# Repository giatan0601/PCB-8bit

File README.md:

# PCB-8bit

Dự án thiết kế mạch in (PCB) cho bộ cộng 8-bit, được xây dựng từ các khối **full adder 1-bit** ghép nối tiếp, kèm theo mạch **giao tiếp (interface)** để nhập dữ liệu và hiển thị kết quả.

## Mục lục

- [Giới thiệu](#giới-thiệu)
- [Cấu trúc thư mục](#cấu-trúc-thư-mục)
- [Nguyên lý hoạt động](#nguyên-lý-hoạt-động)
- [Công cụ sử dụng](#công-cụ-sử-dụng)

- [Hướng dẫn sử dụng](#hướng-dẫn-sử-dụng)
- [Hình ảnh](#hình-ảnh)
- [Tác giả](#tác-giả)

## Giới thiệu

Mục tiêu của dự án là thiết kế và chế tạo một bộ cộng 8-bit trên PCB, theo hướng đi từ khối nhỏ đến hệ thống hoàn chỉnh:

1. Thiết kế và kiểm tra khối full adder 1-bit.
2. Ghép 8 khối full adder thành bộ cộng 8-bit (kiểu ripple-carry).
3. Thiết kế mạch interface để nhập hai toán hạng và quan sát kết quả.

## Cấu trúc thư mục

```
PCB-8bit/
├── fulladder1bit/
│   └── 1bit/          # Thiết kế schematic + PCB của khối full adder 1-bit
└── interface/         # Thiết kế mạch giao tiếp (nhập liệu / hiển thị)
```

| Thư mục | Mô tả |
| --- | --- |
| `fulladder1bit/1bit` | Khối full adder 1-bit, là đơn vị cơ bản để xây dựng bộ cộng 8-bit |
| `interface` | Mạch giao tiếp giữa người dùng và bộ cộng |

## Nguyên lý hoạt động

Mỗi khối full adder 1-bit nhận vào 3 tín hiệu: `A`, `B` và `Cin` (số nhớ từ bit trước), cho ra `Sum` và `Cout` (số nhớ sang bit sau).

**Công thức logic:**

```
Sum  = A ⊕ B ⊕ Cin
Cout = (A · B) + (Cin · (A ⊕ B))
```

**Bảng chân trị:**

| A | B | Cin | Sum | Cout |
|:-:|:-:|:---:|:---:|:----:|
| 0 | 0 | 0 | 0 | 0 |
| 0 | 0 | 1 | 1 | 0 |
| 0 | 1 | 0 | 1 | 0 |
| 0 | 1 | 1 | 0 | 1 |
| 1 | 0 | 0 | 1 | 0 |
| 1 | 0 | 1 | 0 | 1 |
| 1 | 1 | 0 | 0 | 1 |
| 1 | 1 | 1 | 1 | 1 |

**Bộ cộng 8-bit (ripple-carry):** `Cout` của khối thứ *i* được nối vào `Cin` của khối thứ *i+1*. `Cin` của khối đầu tiên nối mức 0.

```
A7 B7      A1 B1      A0 B0
 │  │       │  │       │  │
┌▼──▼┐     ┌▼──▼┐     ┌▼──▼┐
│ FA │ ... │ FA │◄────│ FA │◄── Cin = 0
└┬──┬┘     └┬──┬┘     └┬──┬┘
 │  │       │  │       │  │
Cout S7     C1 S1      C0 S0
```

## Công cụ sử dụng

- Phần mềm thiết kế PCB: `KiCad `

## Hướng dẫn sử dụng

**1. Tải mã nguồn**

```bash
git clone https://github.com/giatan0601/PCB-8bit.git
cd PCB-8bit
```

**2. Mở thiết kế**

- Khối full adder 1-bit: mở project trong thư mục `fulladder1bit/1bit`.
- Mạch giao tiếp: mở project trong thư mục `interface`.

**3. Xuất file sản xuất (Gerber)**

Xuất file Gerber và file khoan từ phần mềm thiết kế, sau đó gửi cho nhà sản xuất PCB.

**4. Kiểm tra mạch**

Cấp nguồn `5V`, đặt các giá trị `A`, `B`, `Cin` và đối chiếu `Sum`, `Cout` với bảng chân trị ở trên.

## Hình ảnh

## Tác giả

- **giatan0601** – [GitHub](https://github.com/giatan0601)

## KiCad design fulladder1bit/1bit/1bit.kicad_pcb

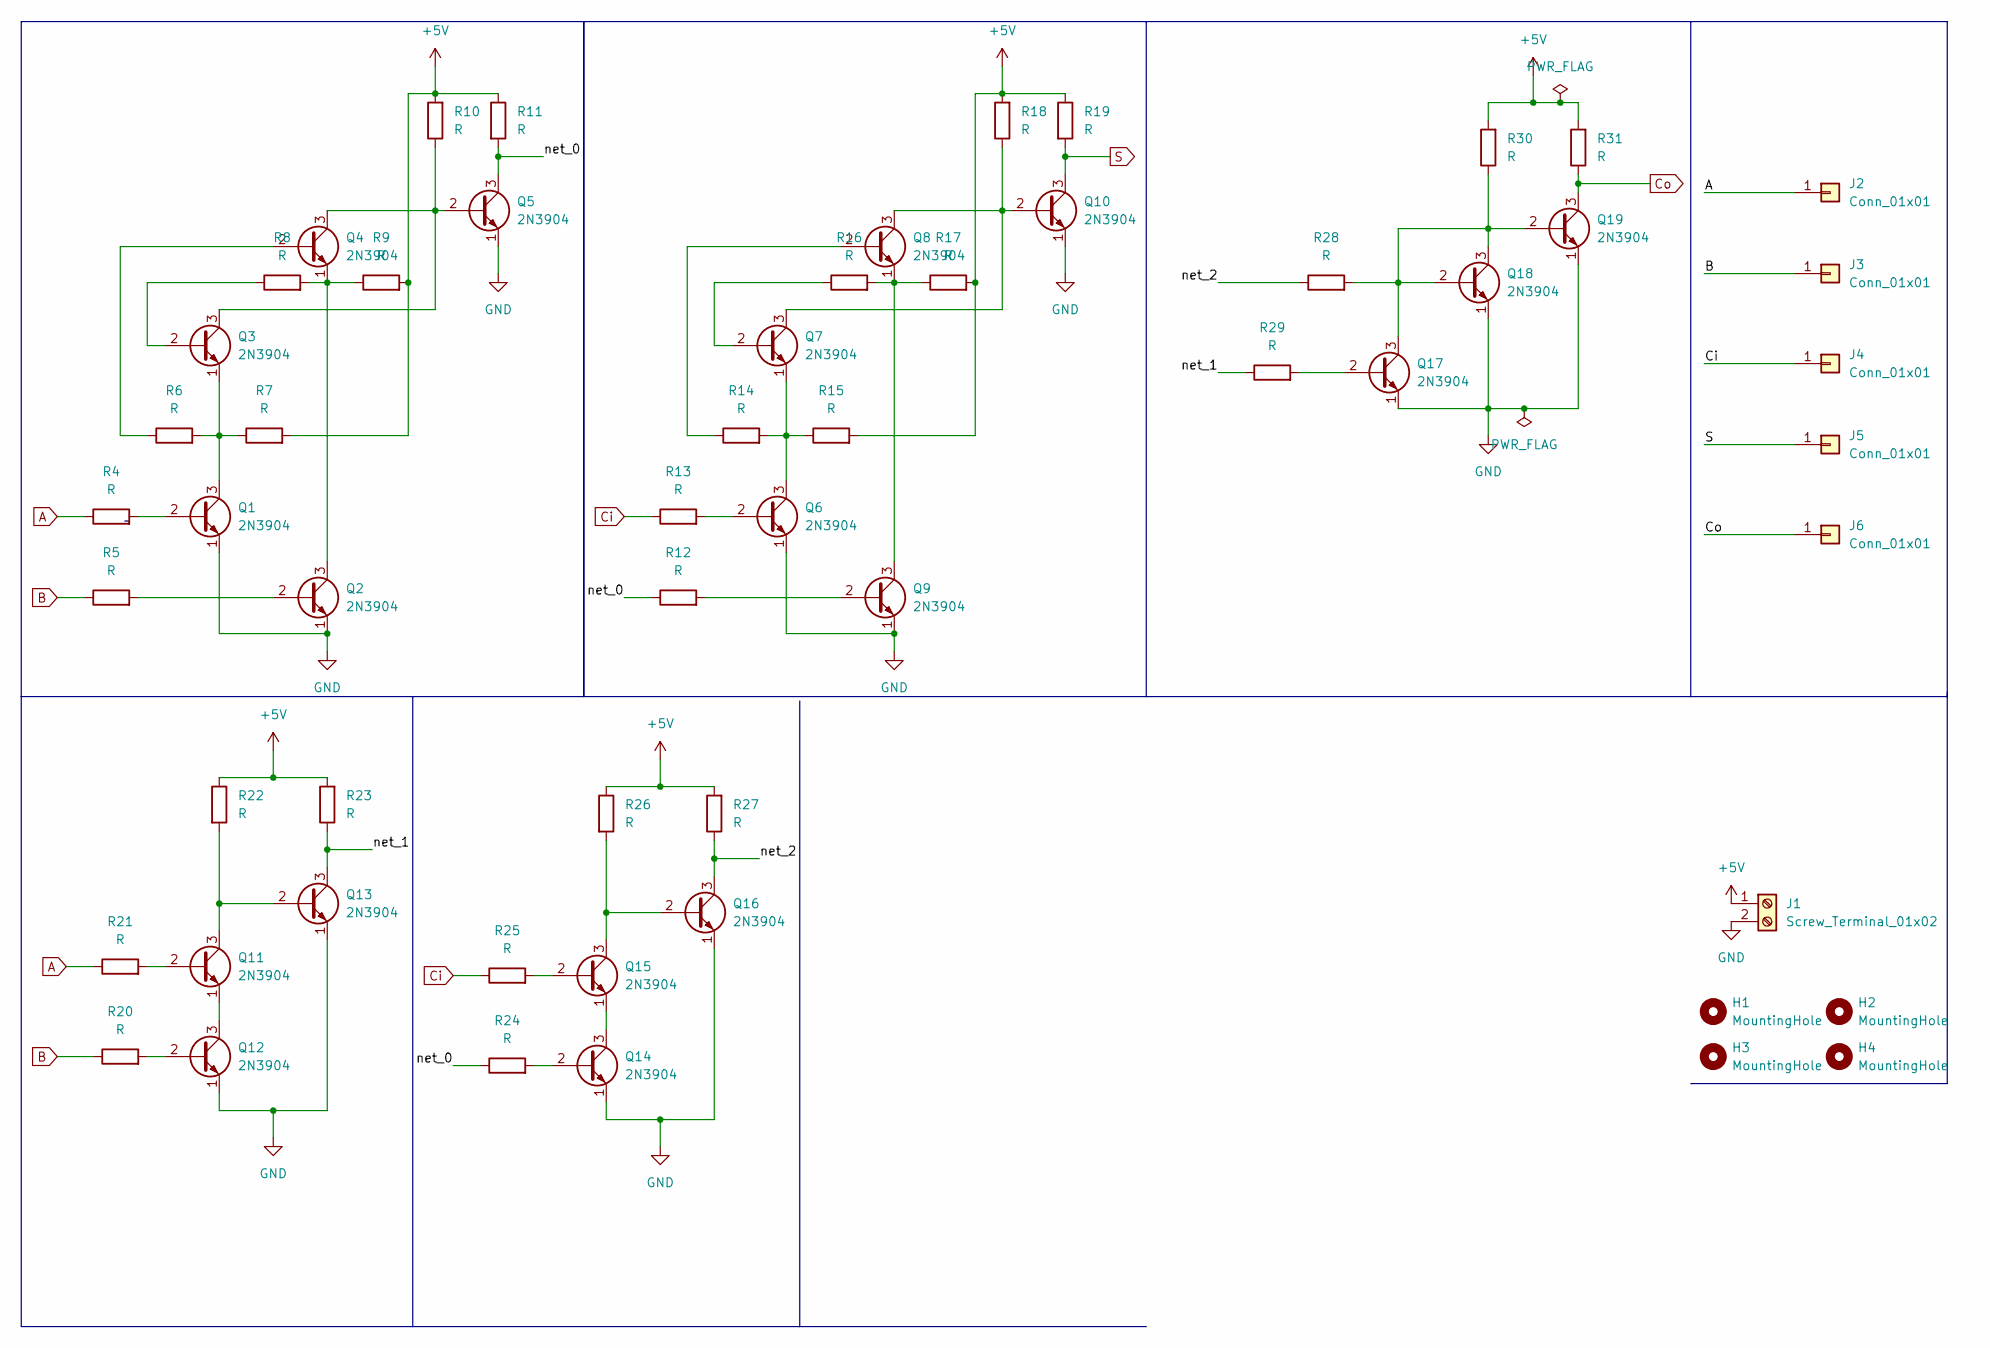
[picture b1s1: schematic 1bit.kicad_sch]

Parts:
H1, H2, H3, H4: MountingHole; MountingHole_2.7mm
J1: Screw_Terminal_01x02; TerminalBlock_Phoenix_MKDS-1,5-2_1x02_P5.00mm_Horizontal
J2, J3, J4, J5, J6: Conn_01x01; PinHeader_1x01_P2.54mm_Horizontal
Q1, Q2, Q3, Q4, Q5, Q6, Q7, Q8, Q9, Q10, Q11, Q12, Q13, Q14, Q15, Q16, Q17, Q18, Q19: 2N3904; TO-92_Inline_Wide
R4, R5, R6, R7, R8, R9, R10, R11, R12, R13, R14, R15, R16, R17, R18, R19, R20, R21, R22, R23, R24, R25, R26, R27, R28, R29, R30, R31: R; R_Axial_DIN0207_L6.3mm_D2.5mm_P7.62mm_Horizontal

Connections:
+5V: J1.1, R7.2, R9.2, R10.2, R11.1, R15.2, R17.2, R18.2, R19.1, R22.1, R23.2, R26.1, R27.2, R30.2, R31.2
/net_0: Q5.3 (C), R11.2, R12.1, R24.1
/net_1: Q13.3 (C), R23.1, R29.1
/net_2: Q16.3 (C), R27.1, R28.1
A: J2.1 (Pin_1_1), R4.1, R21.1
B: J3.1 (Pin_1_1), R5.1, R20.1
Ci: J4.1 (Pin_1_1), R13.1, R25.1
Co: J6.1 (Pin_1_1), Q19.3 (C), R31.1
GND: J1.2, Q1.1 (E), Q2.1 (E), Q5.1 (E), Q6.1 (E), Q9.1 (E), Q10.1 (E), Q12.1 (E), Q13.1 (E), Q14.1 (E), Q16.1 (E), Q17.1 (E), Q18.1 (E), Q19.1 (E)
unnamed: Q1.2 (B), R4.2
unnamed: Q1.3 (C), Q3.1 (E), R6.2, R7.1
unnamed: Q2.2 (B), R5.2
unnamed: Q2.3 (C), Q4.1 (E), R8.2, R9.1
unnamed: Q3.2 (B), R8.1
unnamed: Q3.3 (C), Q4.3 (C), Q5.2 (B), R10.1
unnamed: Q4.2 (B), R6.1
unnamed: Q6.2 (B), R13.2
unnamed: Q6.3 (C), Q7.1 (E), R14.2, R15.1
unnamed: Q7.2 (B), R16.1
unnamed: Q8.2 (B), R14.1
unnamed: Q8.1 (E), Q9.3 (C), R16.2, R17.1
unnamed: Q9.2 (B), R12.2
unnamed: Q7.3 (C), Q8.3 (C), Q10.2 (B), R18.1
unnamed: Q11.2 (B), R21.2
unnamed: Q11.3 (C), Q13.2 (B), R22.2
unnamed: Q11.1 (E), Q12.3 (C)
unnamed: Q12.2 (B), R20.2
unnamed: Q14.2 (B), R24.2
unnamed: Q14.3 (C), Q15.1 (E)
unnamed: Q15.2 (B), R25.2
unnamed: Q15.3 (C), Q16.2 (B), R26.2
unnamed: Q17.2 (B), R29.2
unnamed: Q17.3 (C), Q18.2 (B), Q18.3 (C), Q19.2 (B), R28.2, R30.1
S: J5.1 (Pin_1_1), Q10.3 (C), R19.2

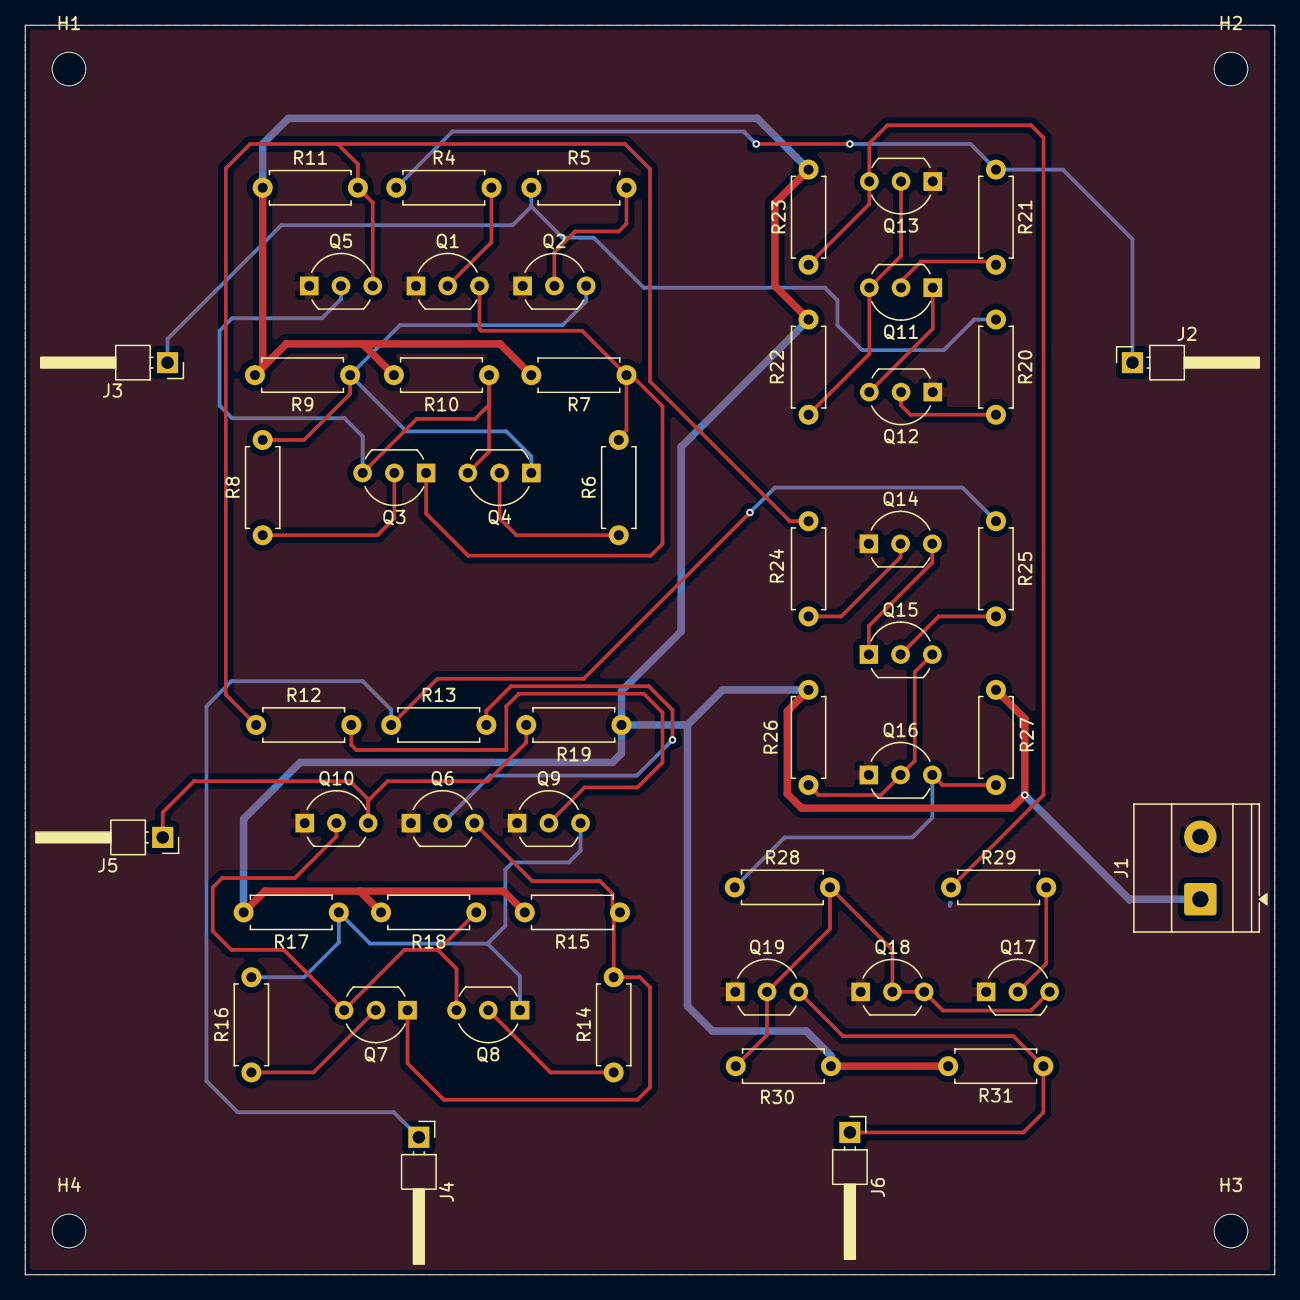
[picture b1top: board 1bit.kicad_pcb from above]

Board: 2 copper layers, 100.0 x 100.0 mm, 57 parts (0 on the bottom side), 34 nets.

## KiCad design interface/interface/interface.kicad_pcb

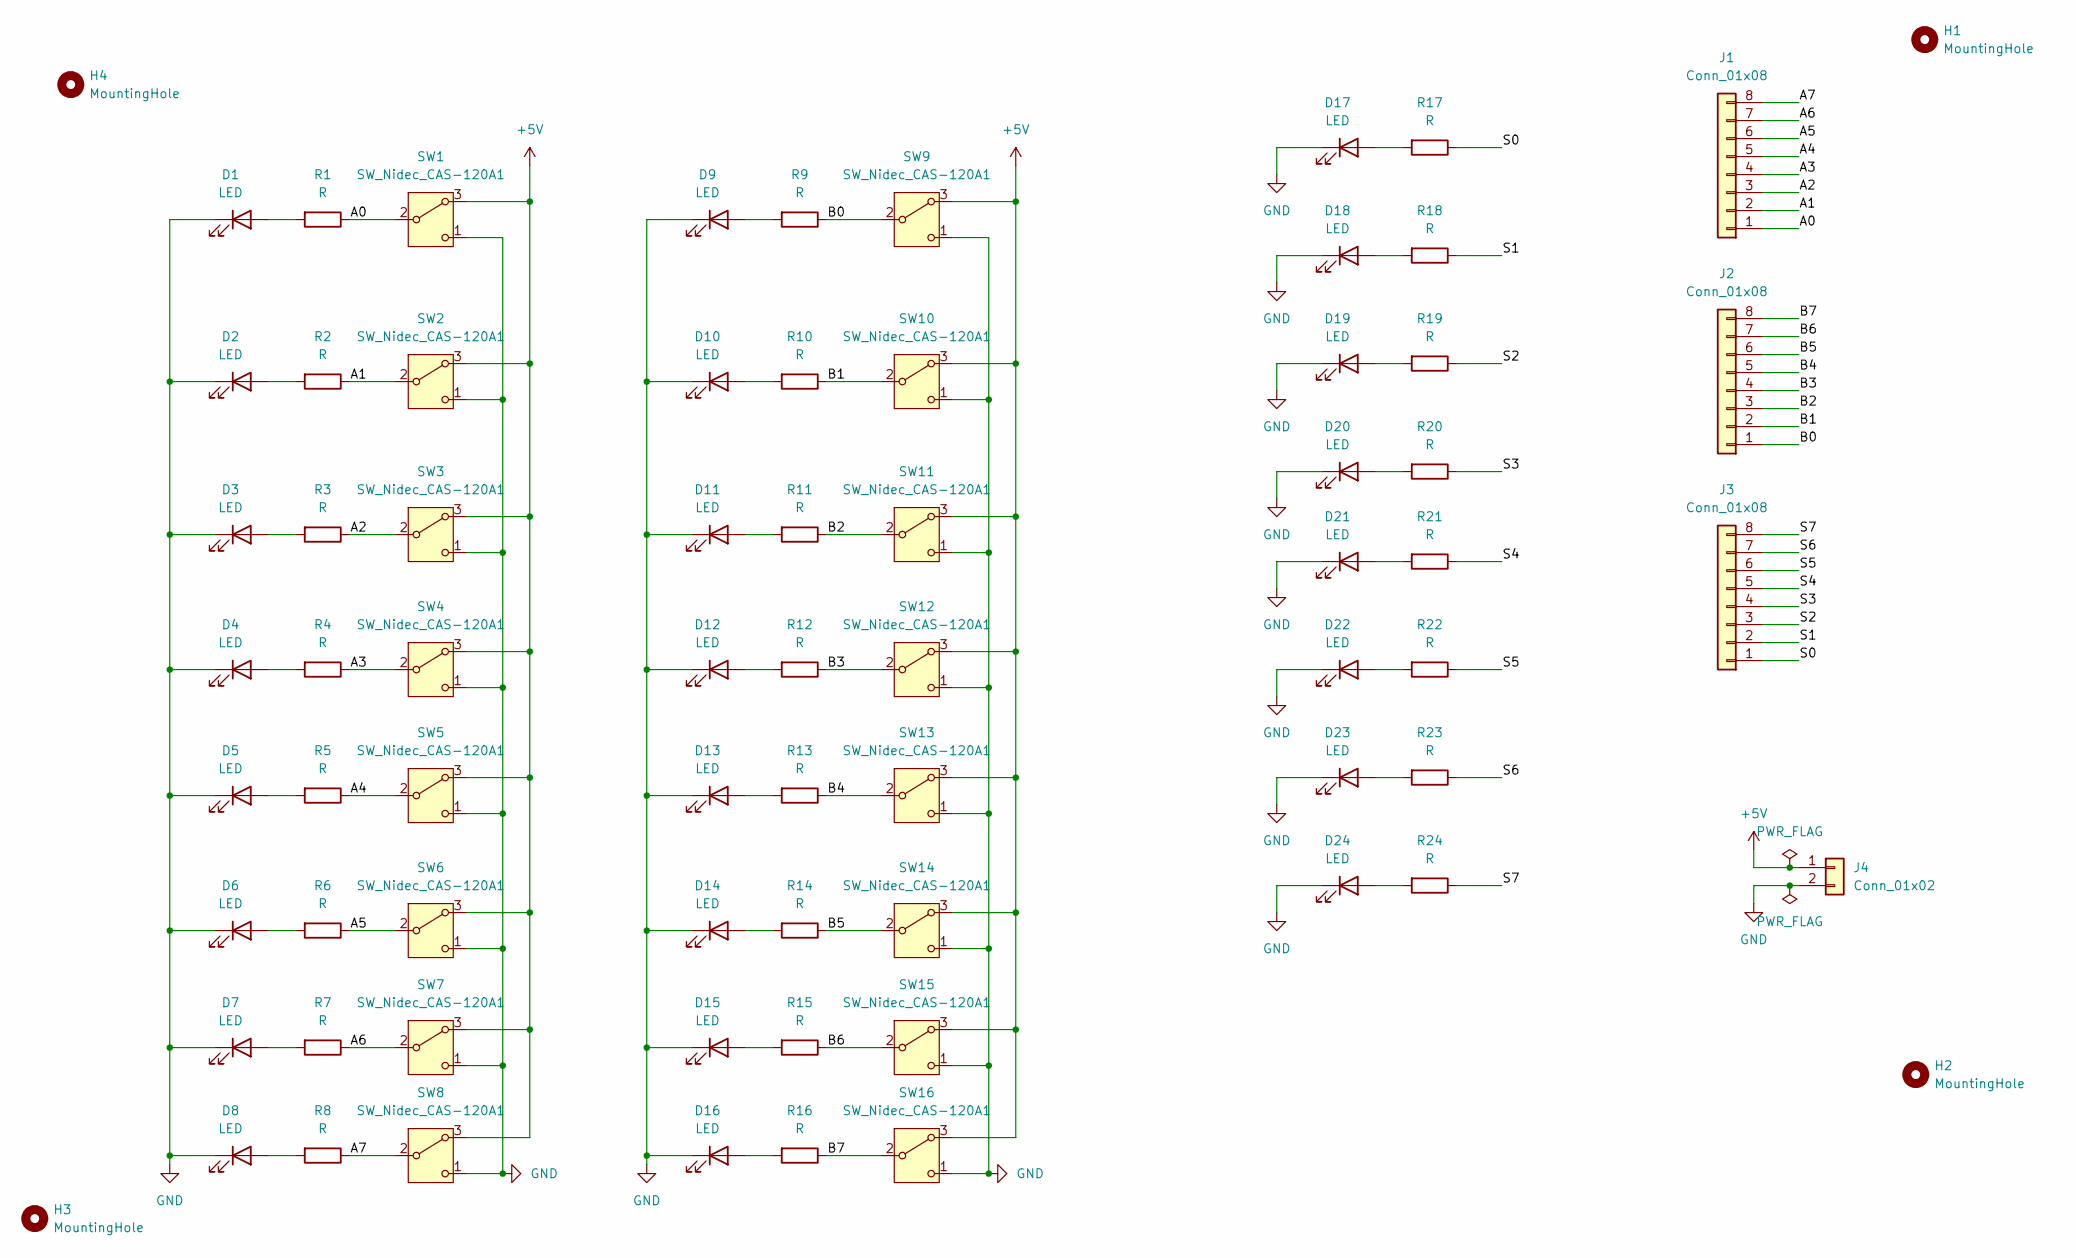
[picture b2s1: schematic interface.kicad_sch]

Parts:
D1, D2, D3, D4, D5, D6, D7, D8, D9, D10, D11, D12, D13, D14, D15, D16, D17, D18, D19, D20, D21, D22, D23, D24: LED; LED_D3.0mm
H1, H2, H3, H4: MountingHole; MountingHole_3.2mm_M3
J1, J2, J3: Conn_01x08; PinHeader_1x08_P2.54mm_Vertical
J4: Conn_01x02; TerminalBlock_Phoenix_MKDS-1,5-2_1x02_P5.00mm_Horizontal
R1, R2, R3, R4, R5, R6, R7, R8, R9, R10, R11, R12, R13, R14, R15, R16, R17, R18, R19, R20, R21, R22, R23, R24: R; R_Axial_DIN0207_L6.3mm_D2.5mm_P10.16mm_Horizontal
SW1, SW2, SW3, SW4, SW5, SW6, SW7, SW8, SW9, SW10, SW11, SW12, SW13, SW14, SW15, SW16: SW_Nidec_CAS-120A1; SW_SS12D07VG4

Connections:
+5V: J4.1, SW1.3 (A), SW2.3 (A), SW3.3 (A), SW4.3 (A), SW5.3 (A), SW6.3 (A), SW7.3 (A), SW8.3 (A), SW9.3 (A), SW10.3 (A), SW11.3 (A), SW12.3 (A), SW13.3 (A), SW14.3 (A), SW15.3 (A), SW16.3 (A)
/A0: J1.1, R1.1, SW1.2 (B)
/A1: J1.2, R2.1, SW2.2 (B)
/A2: J1.3, R3.1, SW3.2 (B)
/A3: J1.4, R4.1, SW4.2 (B)
/A4: J1.5, R5.1, SW5.2 (B)
/A5: J1.6, R6.1, SW6.2 (B)
/A6: J1.7, R7.1, SW7.2 (B)
/A7: J1.8, R8.1, SW8.2 (B)
/B0: J2.1, R9.1, SW9.2 (B)
/B1: J2.2, R10.1, SW10.2 (B)
/B2: J2.3, R11.1, SW11.2 (B)
/B3: J2.4, R12.1, SW12.2 (B)
/B4: J2.5, R13.1, SW13.2 (B)
/B5: J2.6, R14.1, SW14.2 (B)
/B6: J2.7, R15.1, SW15.2 (B)
/B7: J2.8, R16.1, SW16.2 (B)
/S0: J3.1, R17.1
/S1: J3.2, R18.1
/S2: J3.3, R19.1
/S3: J3.4, R20.1
/S4: J3.5, R21.1
/S5: J3.6, R22.1
/S6: J3.7, R23.1
/S7: J3.8, R24.1
GND: D1.1 (K), D2.1 (K), D3.1 (K), D4.1 (K), D5.1 (K), D6.1 (K), D7.1 (K), D8.1 (K), D9.1 (K), D10.1 (K), D11.1 (K), D12.1 (K), D13.1 (K), D14.1 (K), D15.1 (K), D16.1 (K), D17.1 (K), D18.1 (K), D19.1 (K), D20.1 (K), D21.1 (K), D22.1 (K), D23.1 (K), D24.1 (K), J4.2, SW1.1 (C), SW2.1 (C), SW3.1 (C), SW4.1 (C), SW5.1 (C), SW6.1 (C), SW7.1 (C), SW8.1 (C), SW9.1 (C), SW10.1 (C), SW11.1 (C), SW12.1 (C), SW13.1 (C), SW14.1 (C), SW15.1 (C), SW16.1 (C)
unnamed: D1.2 (A), R1.2
unnamed: D2.2 (A), R2.2
unnamed: D3.2 (A), R3.2
unnamed: D4.2 (A), R4.2
unnamed: D5.2 (A), R5.2
unnamed: D6.2 (A), R6.2
unnamed: D7.2 (A), R7.2
unnamed: D8.2 (A), R8.2
unnamed: D9.2 (A), R9.2
unnamed: D10.2 (A), R10.2
unnamed: D11.2 (A), R11.2
unnamed: D12.2 (A), R12.2
unnamed: D13.2 (A), R13.2
unnamed: D14.2 (A), R14.2
unnamed: D15.2 (A), R15.2
unnamed: D16.2 (A), R16.2
unnamed: D17.2 (A), R17.2
unnamed: D18.2 (A), R18.2
unnamed: D19.2 (A), R19.2
unnamed: D20.2 (A), R20.2
unnamed: D21.2 (A), R21.2
unnamed: D22.2 (A), R22.2
unnamed: D23.2 (A), R23.2
unnamed: D24.2 (A), R24.2

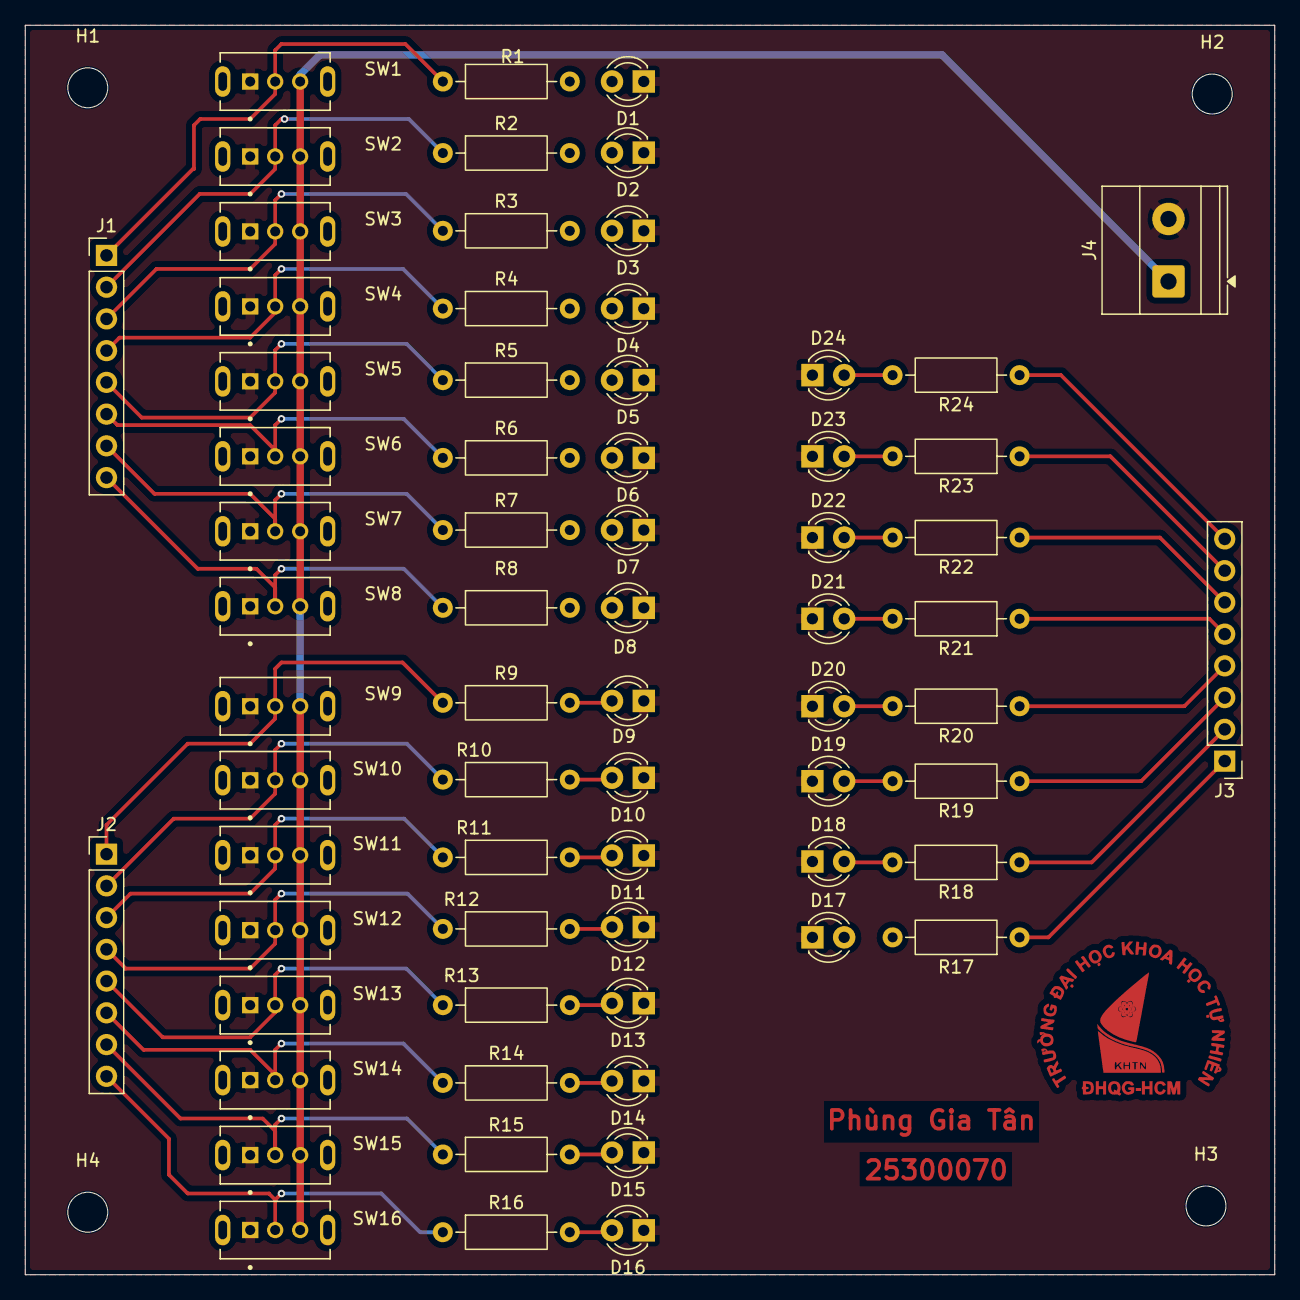
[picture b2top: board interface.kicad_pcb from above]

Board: 2 copper layers, 100.0 x 100.0 mm, 72 parts (0 on the bottom side), 50 nets.
